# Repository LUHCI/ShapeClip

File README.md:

# ShapeClip

## Towards Rapid Prototyping with Shape-Changing Displays for Designers

ShapeClip is a modular tool capable of transforming any computer screen into a z-actuating shape-changing display. This enables designers to produce dynamic physical forms by simply ‘clipping’ actuators onto screens.

ShapeClip displays are portable, scalable, fault-tolerant, and support runtime actuator re-arrangement. Users are not required to have knowledge of electronics or programming, and can develop motion designs with presentation software, image editors, and for those who require more control, web-standard interfaces.

## Getting Started

There are 4 main software packages included here:

1. [Clip Firmware](../master/00_Firmware/Firmware/Firmware.ino) + [Servo Extensions](../Slider/00_Firmware/Firmware/Firmware.ino)
2. [Websocket/Serial Bridge](../master/10_Driver/wsserial)
3. [SUR40 Clip Detector (OpenCV)](../master/15_Middleware/ShapeClipDetector)
4. [Javascript API](../master/10_Driver/ShapeClipAPI.js)
5. [Web-based Sample Apps](../master/20_Applications)

In terms of software that can be used to create motion designs, ShapeClip is not restricted to any particular software package. You are free to work with the tools you know.

To get started you will need to get your hands on some ShapeClip hardware.To do that, you can view our design documents in the 01_Hardware folder.

The following image is a trace (from Eagle) of the ShapeClip mkIII board. The different colours denote different layers of the circuit.

Each standard Clip weighs ≈30g, and is 20×20×80mm when closed, and costs ≈USD$15. The selected stepper motor has 60mm of travel. Under stress, individual Clips draw between 60–540mA at 5V, enabling small groups to be powered via USB. When powering larger numbers, be sure not to make the chain of clips too long as you may damage the Clips. Clips are connected together with pin connectors that double up as a power transmission method. When the Clip is held upright, the top two pins of the power connector are +5v and the bottom one is GND. The motor and circuit logic are kept separate in the top two pins, but in most scenarios they can share power.

## Research

This work was conducted as part of the GHOST project (http://ghostfet-prod.cs.bris.ac.uk/) to further the understanding of shape-changing computer interfaces.

You can view our paper (CHI2015) online here. To cite the paper, use the following citation: ...

## License

Copyright (c) Lancaster University, GHOST Project

Permission is hereby granted, free of charge, to any person obtaining a copy of this software and associated documentation files (the "Software"), to deal in the Software without restriction, including without limitation the rights to use, copy, modify, merge, publish, distribute, sublicense, and/or sell copies of the Software, and to permit persons to whom the Software is furnished to do so, subject to the following conditions:

The above copyright notice and this permission notice shall be included in all copies or substantial portions of the Software.

THE SOFTWARE IS PROVIDED "AS IS", WITHOUT WARRANTY OF ANY KIND, EXPRESS OR IMPLIED, INCLUDING BUT NOT LIMITED TO THE WARRANTIES OF MERCHANTABILITY, FITNESS FOR A PARTICULAR PURPOSE AND NONINFRINGEMENT. IN NO EVENT SHALL THE AUTHORS OR COPYRIGHT HOLDERS BE LIABLE FOR ANY CLAIM, DAMAGES OR OTHER LIABILITY, WHETHER IN AN ACTION OF CONTRACT, TORT OR OTHERWISE, ARISING FROM, OUT OF OR IN CONNECTION WITH THE SOFTWARE OR THE USE OR OTHER DEALINGS IN THE SOFTWARE.

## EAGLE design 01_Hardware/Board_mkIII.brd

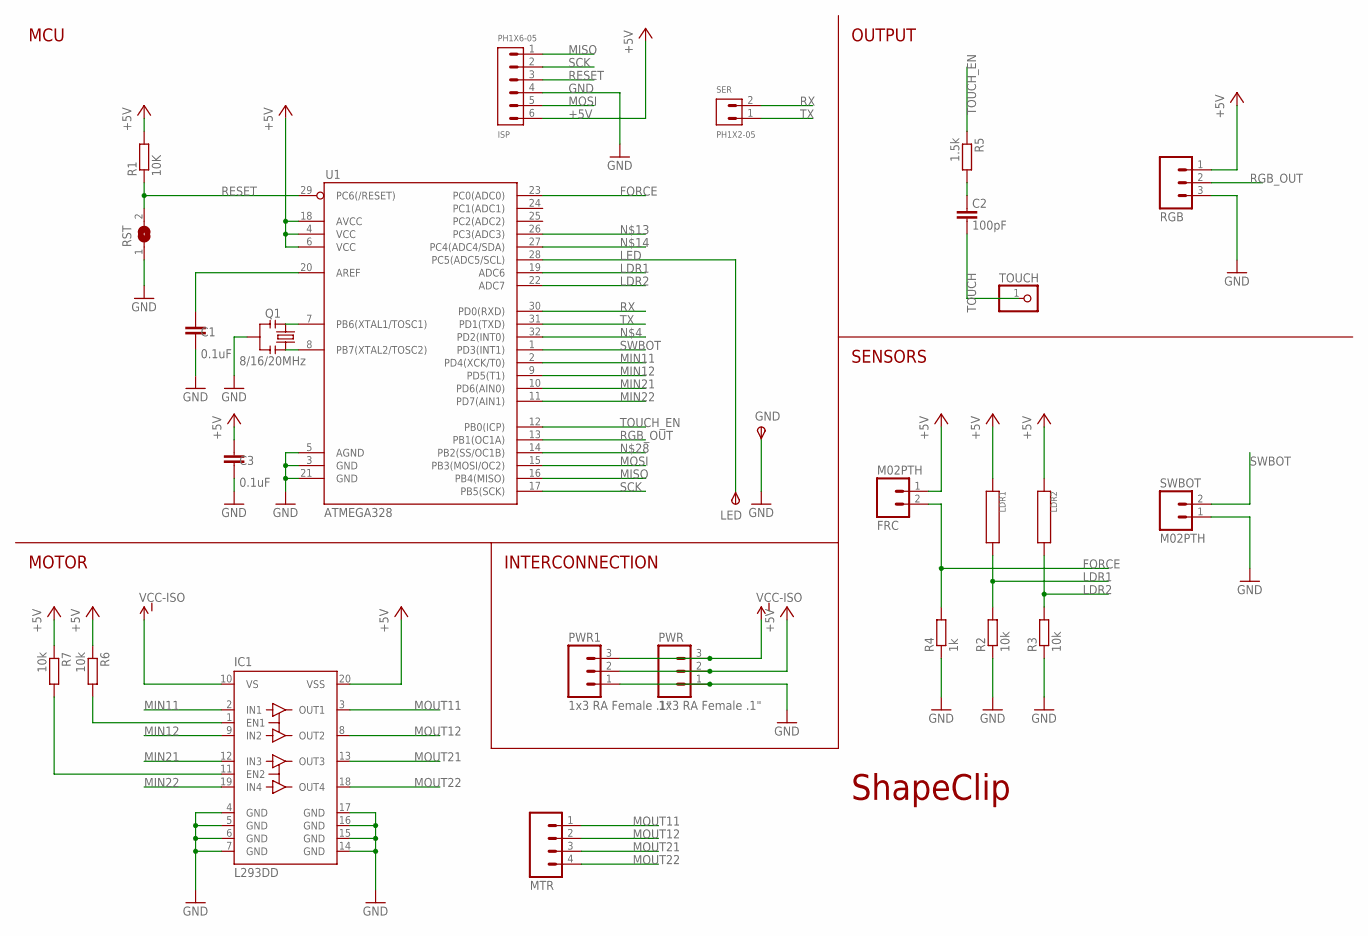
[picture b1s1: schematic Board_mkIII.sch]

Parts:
C1, C3: 0.1uF; C0603
C2: 100pF; C0603
FRC: M02PTH; 1X02
GND: TPSTP20SQ; TP20SQ
IC1: L293DD; SO20
ISP: PH1X6-05; PH005-1-6
LDR1, LDR2: DR3-31-LDRLONG; DR3-31-LDR_L
LED: TPSTP20SQ; TP20SQ
MTR: M04PTH; 1X04
PWR, PWR1: 1x3 RA Female .1"; PHD_FEMALE_3_90DEG
Q1: 8/16/20MHz; RESONATOR-SMD
R1: 10K; R0603
R2, R3, R6, R7: 10k; R0603
R4: 1k; R0603
R5: 1.5k; R0603
RGB: M03PTH; 1X03
RST: SJW
SER: PH1X2-05; PH005-1-2
SWBOT: M02PTH; 1X02
TOUCH: PINHD-1X1; 1X01
U1: ATMEGA328; TQFP32-08

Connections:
+5V: C3.2, FRC.1, IC1.20 (VSS), ISP.6, LDR1.1, LDR2.1, PWR.2, PWR1.2, R1.2, R6.1, R7.1, RGB.1, U1.4 (VCC), U1.6 (VCC), U1.18 (AVCC)
FORCE: FRC.2, R4.2, U1.23 (PC0(ADC0))
GND: C1.1, C3.1, GND.TP, IC1.4 (GND), IC1.5 (GND), IC1.6 (GND), IC1.7 (GND), IC1.14 (GND), IC1.15 (GND), IC1.16 (GND), IC1.17 (GND), ISP.4, PWR.1, PWR1.1, Q1.2, R2.1, R3.1, R4.1, RGB.3, RST.1, SWBOT.1, U1.3 (GND), U1.5 (AGND), U1.21 (GND)
LDR1: LDR1.2, R2.2, U1.19 (ADC6)
LDR2: LDR2.2, R3.2, U1.22 (ADC7)
LED: LED.TP, U1.28 (PC5(ADC5/SCL))
MIN11: IC1.2 (IN1), U1.2 (PD4(XCK/T0))
MIN12: IC1.9 (IN2), U1.9 (PD5(T1))
MIN21: IC1.12 (IN3), U1.10 (PD6(AIN0))
MIN22: IC1.19 (IN4), U1.11 (PD7(AIN1))
MISO: ISP.1, U1.16 (PB4(MISO))
MOSI: ISP.5, U1.15 (PB3(MOSI/OC2))
MOUT11: IC1.3 (OUT1), MTR.1
MOUT12: IC1.8 (OUT2), MTR.2
MOUT21: IC1.13 (OUT3), MTR.3
MOUT22: IC1.18 (OUT4), MTR.4
unnamed: Q1.1, U1.8 (PB7(XTAL2/TOSC2))
unnamed: Q1.3, U1.7 (PB6(XTAL1/TOSC1))
unnamed: C1.2, U1.20 (AREF)
unnamed: C2.2, R5.2
unnamed: IC1.1 (EN1), R6.2
unnamed: IC1.11 (EN2), R7.2
RESET: ISP.3, R1.1, RST.2, U1.29 (PC6(/RESET))
RGB_OUT: RGB.2, U1.13 (PB1(OC1A))
RX: SER.2, U1.30 (PD0(RXD))
SCK: ISP.2, U1.17 (PB5(SCK))
SWBOT: SWBOT.2, U1.1 (PD3(INT1))
TOUCH: C2.1, TOUCH.1
TOUCH_EN: R5.1, U1.12 (PB0(ICP))
TX: SER.1, U1.31 (PD1(TXD))
VCC-ISO: IC1.10 (VS), PWR.3, PWR1.3

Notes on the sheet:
MCU
MOTOR
SENSORS
OUTPUT
INTERCONNECTION
ShapeClip

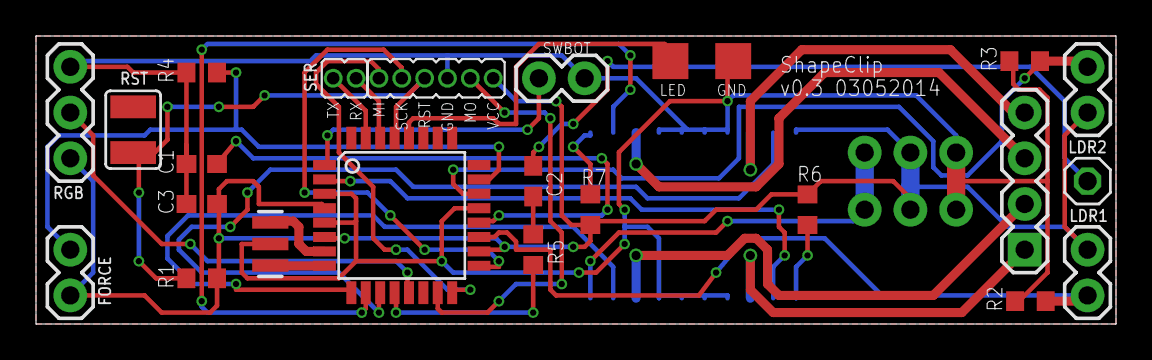
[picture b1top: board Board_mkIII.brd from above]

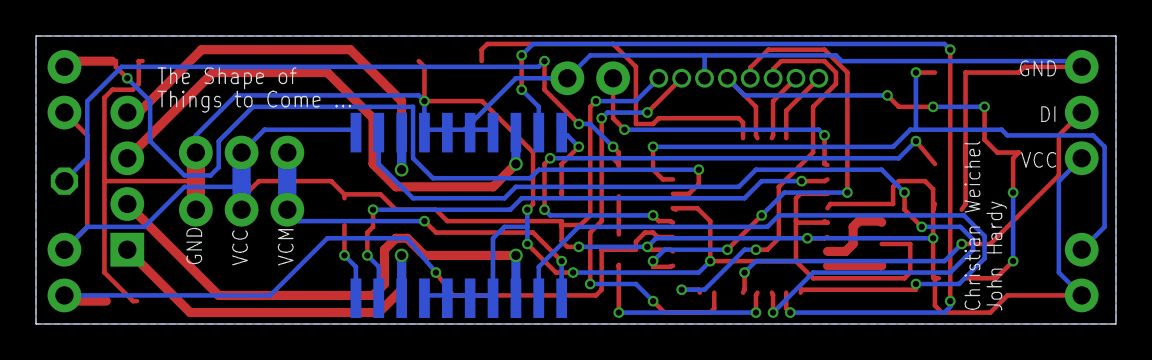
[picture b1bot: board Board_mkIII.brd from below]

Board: 2 copper layers, 60.0 x 16.0 mm, 27 parts (2 on the bottom side), 31 nets.

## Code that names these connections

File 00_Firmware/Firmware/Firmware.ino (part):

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/* IO Pins */
#define PIN_LED   A5		// The on-board LED.
#define PIN_SWTOP 2			// The top switch (digital).
#define PIN_SWBOT 3			// The bottom switch (digital).
#define PIN_FORCE A0		// The force input (analog).
#define PIN_TOUCH 8  		// The touch output (digital).
#define PIN_RGB_OUT 9		// The RGB LED (digital).
#define PIN_MIN11 4			// Motor Coil 1 + (digital).
#define PIN_MIN12 5			// Motor Coil 1 - (digital).
#define PIN_MIN21 6			// Motor Coil 2 + (digital).
#define PIN_MIN22 7			// Motor Coil 2 - (digital).
#define PIN_RND   A4		// Random data source pin.
#define PIN_LDR1  A6		// The LDR1 input (analog).
#define PIN_LDR2  A7		// The LDR2 input (analog).


/* Actuation Type */
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	#define ACTUATOR_MAX STEPPER_TRAVEL		// Maximum position/angle/speed of the actuator.
	#define ACTUATOR_MIN 0					// Minimum position/angle/speed of the actuator.
	
	Stepper motor(STEPPER_ANGLE, PIN_MIN11, PIN_MIN12, PIN_MIN21, PIN_MIN22);
	boolean bMotorCalibrated = false;	// Is the motor position value accurate?
	
	/** Set up the motor. Called once when the device starts. */
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	void configureActuator() {
		
		// Motor pins as output.
		pinMode(PIN_MIN11, OUTPUT);
		pinMode(PIN_MIN12, OUTPUT);
		pinMode(PIN_MIN21, OUTPUT);
		pinMode(PIN_MIN22, OUTPUT);
	}
	
	/** Actuate based on the target values set. */
	void actuate() {
		
		// Read the current value.
		int adc = analogRead(PIN_TOUCH);
		iActuatorTarget = constrain(map(adc, SLIDER_ADC_MIN, SLIDER_ADC_MAX, ACTUATOR_MIN, ACTUATOR_MAX), ACTUATOR_MIN, ACTUATOR_MAX);
		
		// PID current to match target.
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	
	/** Set up the slider. Called once when the device starts. */
	void configureActuator() {
		servo.attach(PIN_TOUCH);	// Re-use the touch out pin (digital).
	}
	
	/** Actuate based on the target values set. */
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	void configureActuator() {
		
		// Motor pins as output.
		pinMode(PIN_MIN11, OUTPUT);
		pinMode(PIN_MIN12, OUTPUT);
		pinMode(PIN_MIN21, OUTPUT);
		pinMode(PIN_MIN22, OUTPUT);
	}
	
	/** Actuate based on the target values set. */
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//#define SSMODE_CMDPRINT		// Screen serial mode: Enable serial print of command buffer interpretations.
//#define SSMODE_STREAMPRINT	// Screen serial mode: Enable serial print of bitstream data for debugging the serial connection.  <-- this one is cool
//#define SSMODE_TRANSMISSION_GRAPH // Print out the data for the screen-serial transmission graph.
//#define SERIAL_INFO			// Should device values be streamed via serial? csv: ms, ldr1, ldr2, rgb, height, frc, haspulse, swbot
//#define SERIAL_SYNC_DEBUG		// Should sync pulse debug data be streamed via serial? csv: ms, r, g, b
//#define SERIAL_SYNC_DEBUG2	// Should the verbose sync pulse debug data be streamed via serial? csv: ms, slope, max, r, g, b, min, raw
//#define EMIT_MODES
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

// ShapeClip v1 controls and live values.
Adafruit_NeoPixel pRGB = Adafruit_NeoPixel(1, PIN_RGB_OUT, NEO_GRB + NEO_KHZ800);
LDR ldr1(PIN_LDR1);
LDR ldr2(PIN_LDR2);

int eClipMode = EEMODE_SYNCPULSE;	// Current Clip mode.
int eRGBMode = RGBMODE_NONE;		// Current RGB mode.
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	pinMode(PIN_LED, OUTPUT);
	digitalWrite(PIN_LED, LOW);
	
	// LDR1 and LDR2 (input). NOT REQUIRED FOR ANALOG PINS - MAYBE HARMFUL
	//pinMode(PIN_LDR1, INPUT);
	//pinMode(PIN_LDR2, INPUT);
	
	// Top and bottom switches (input, active).
	pinMode(PIN_SWTOP, INPUT);
	digitalWrite(PIN_SWTOP, HIGH);
	pinMode(PIN_SWBOT, INPUT);
	digitalWrite(PIN_SWBOT, HIGH);
	
	// Touch sensor (output, low).
	pinMode(PIN_TOUCH, OUTPUT);
	digitalWrite(PIN_TOUCH, LOW);
	
	// Force sensor (input).
	pinMode(PIN_FORCE, INPUT);
	
	// Set up the motor.
	configureActuator();
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void detectAndSetModeChange( int skipToMode ) {
	
	// If SWBOT is not pressed, skip out.
	if( digitalRead(PIN_SWBOT) == HIGH && skipToMode == 0 )
		return;
	
	// While we are still holding SWBOT down.
	while( skipToMode == 0 && digitalRead(PIN_SWBOT) == LOW )
	{
		// Swap mode.
		switch( eClipMode )
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	static long iLastMinima = 0;	// The time of the last minimal (ms).

	// Read the LDR and reset the serial debug colour values.
	int iLDRValue = analogRead(PIN_LDR1);
	r=0; g=0; b=0;

	// Compute the slope (dLDR/dTime) by comparing it to the previous data.
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	{
		// Write out values.
		Serial.print(millis()); Serial.print(","); 									// ms
		Serial.print(analogRead(PIN_LDR1)); Serial.print(","); 						// ldr1
		Serial.print(ldr2.sample()); Serial.print(","); 							// ldr2
		Serial.print(RGB(iTargetR, iTargetG, iTargetB), HEX); Serial.print(" "); 	// RGB
		Serial.print(pRGB.getPixelColor(0), HEX); Serial.print(","); 				// RGB
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		Serial.print(getActuatorCurrent()); Serial.print(","); 							// current height
		
		//Serial.print(iMotorPosition); Serial.print(","); 							// current height
		//Serial.print(analogRead(PIN_FORCE)); Serial.print(","); 					// force
		
		//Serial.print(iTargetPos); Serial.print(","); 								// target height
		Serial.print(getActuatorTarget()); Serial.print(","); 								// target height
		Serial.print(bOnScreen ? "Y" : "N"); Serial.print(","); 					// has sync pulse
		Serial.print(digitalRead(PIN_SWBOT) == 0 ? "Y" : "N"); Serial.print("\n");	// swbot
	}
	#endif
}
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	#define SYMB_HIGH 2
	
	// Read the data from the LDRs into an array.
	int iLDRValue[] = { analogRead( PIN_LDR1 ), analogRead( PIN_LDR2 ) };
	int iInVal = iLDRValue[0] - iLDRValue[1];
	
	// Cacluate the midpoint.
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			case 'i':	// INFORMATION
				{
					Serial.print(millis()); Serial.print(","); 				// ShapeClip time in ms.
					Serial.print(analogRead(PIN_FORCE)); Serial.print(","); // Force reading.
					
					Serial.print(getActuatorTarget()); Serial.print(","); 		// Current MOTOR HEIGHT.
					//Serial.print(iMotorPosition); Serial.print(","); 		// Current MOTOR HEIGHT.
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
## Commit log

2014-03-31 Added the hardware
    So far only the schematics and board
2014-03-31 Height is in the synch pulse now
2014-03-31 Implemented the method. This is not working!
2014-03-31 Motor now shutdowns correctly - makes it smooth like butter
2014-03-31 Fixed a LDR mapMinMax bug
    Now constraining the value to from/to
2014-03-31 Implemented color interpolation
2014-04-01 Common Driver Code
    Pulled out the driver code and got the examples pulled out too.
2014-04-08 Starting the experimental transfer mode
2014-04-08 Counterpart
2014-04-09 FW- Height mode FW- Interpolation FW- Motor Shutdown Driver- Height Mode Driver- Apps Folder FW- Motor accuracy improvement
2014-04-09 Start in height only mode.
2014-04-10 Pseudo-working serial comms
2014-04-10 driver matches faster comms
2014-04-10 Web Socket Serial Bridge, Profiling Firmware Mode
    Also added the pack and unpack stuff to the test driver and upgraded all
    the parts to set new target values.
2014-04-10 stuff
2014-04-10 Character protocol
    R/G/B set on serial comms
    Bit Packing
2014-04-10 8-bit protocol
    R/G/B
2014-04-10 closer
2014-04-12 Fixed serial bugs, changed diff drive state interpreter, begun upgrading API.
2014-04-12 updates to serial api js side
2014-04-12 Serial firmware commands back in
2014-04-12 Firmware v2.1
    Removed dud reference files
    Refactored JS API to merge serial comms in
2014-04-12 Firmware v2.1 debug commented out
2014-04-12 Firmware v2.2 Motor Accumulator
2014-04-12 Added agressive motor cooling patch
    Keeping at 2.2 (since all clips upgraded)
2014-04-12 profiler sa=tarted
2014-04-12 API document ready fix
2014-04-12 usage agent
2014-04-12 PPIs
2014-04-12 User agents
2014-04-12 Tweaking
2014-04-12 v2.3 Fixed serial RGB display... whoops
2014-04-13 Grid check
2014-04-13 Profiler updates
2014-04-13 Profiler
2014-04-13 Profiler almost there
2014-04-13 Sync pulse profile start
2014-04-13 Pulse profiler
2014-04-13 asasd
2014-04-13 z\sx
2014-04-13 values
2014-04-13 Almost
2014-04-13 Math.abs
2014-04-13 Bar width
2014-04-13 unconstrainted error axis
2014-04-13 Longer sample frames
2014-04-14 Slower but better quality sample
2014-04-14 Reduced sample times
2014-04-14 Sample resolution incrase
2014-04-14 New colour space
2014-04-14 Split serial comms into receive and loop, changed symantics of mode detector slightly
2014-04-14 Added mode changing via screen-serial when in -ANY-MODE-
2014-04-14 Changed command z to command Z to be in-line with the other screen serial commands
2014-04-14 Logging
    Logging stuff
2014-04-14 Serial mode changes
    Serial commands now work on all modes
2014-04-14 Final Firmware?! Version 2.5
    Looks like a working build! Did minor tweaks to height mode
2014-04-15 Population graphics
2014-04-15 Shape Clip Applications
2014-04-15 Population map (not finished)
2014-04-16 apps
2014-04-16 Magazine change
2014-04-23 Latest Firmware (as submitted)
2014-09-08 Added #ifdef for different actuator types
2014-09-09 Lib updates
2014-09-14 Updated board file
2014-12-27 Update LICENSE

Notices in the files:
parts and their libraries:
SparkFun-FreqCtrl: Licensing: CC v3.0 Share-Alike You are welcome to use this library for commercial purposes.
